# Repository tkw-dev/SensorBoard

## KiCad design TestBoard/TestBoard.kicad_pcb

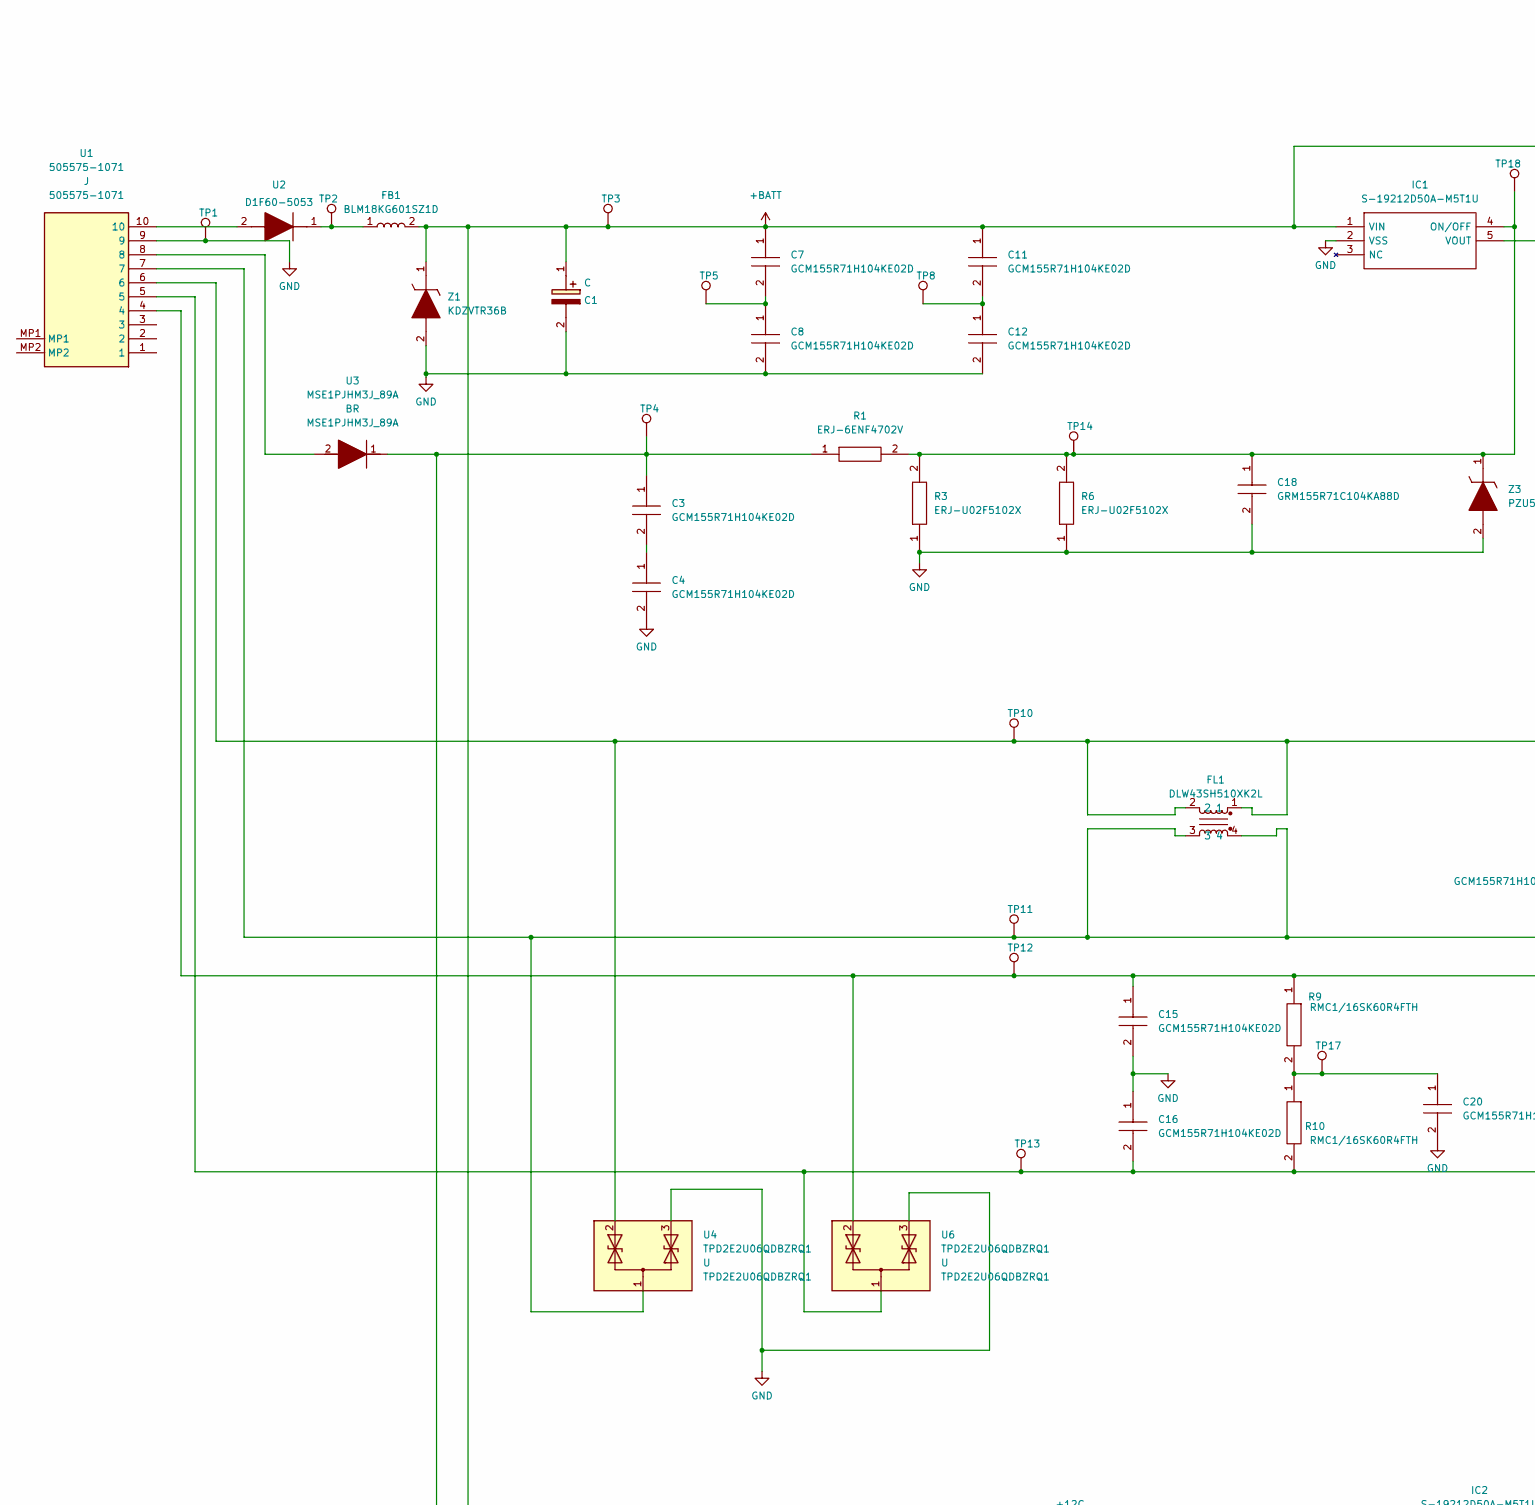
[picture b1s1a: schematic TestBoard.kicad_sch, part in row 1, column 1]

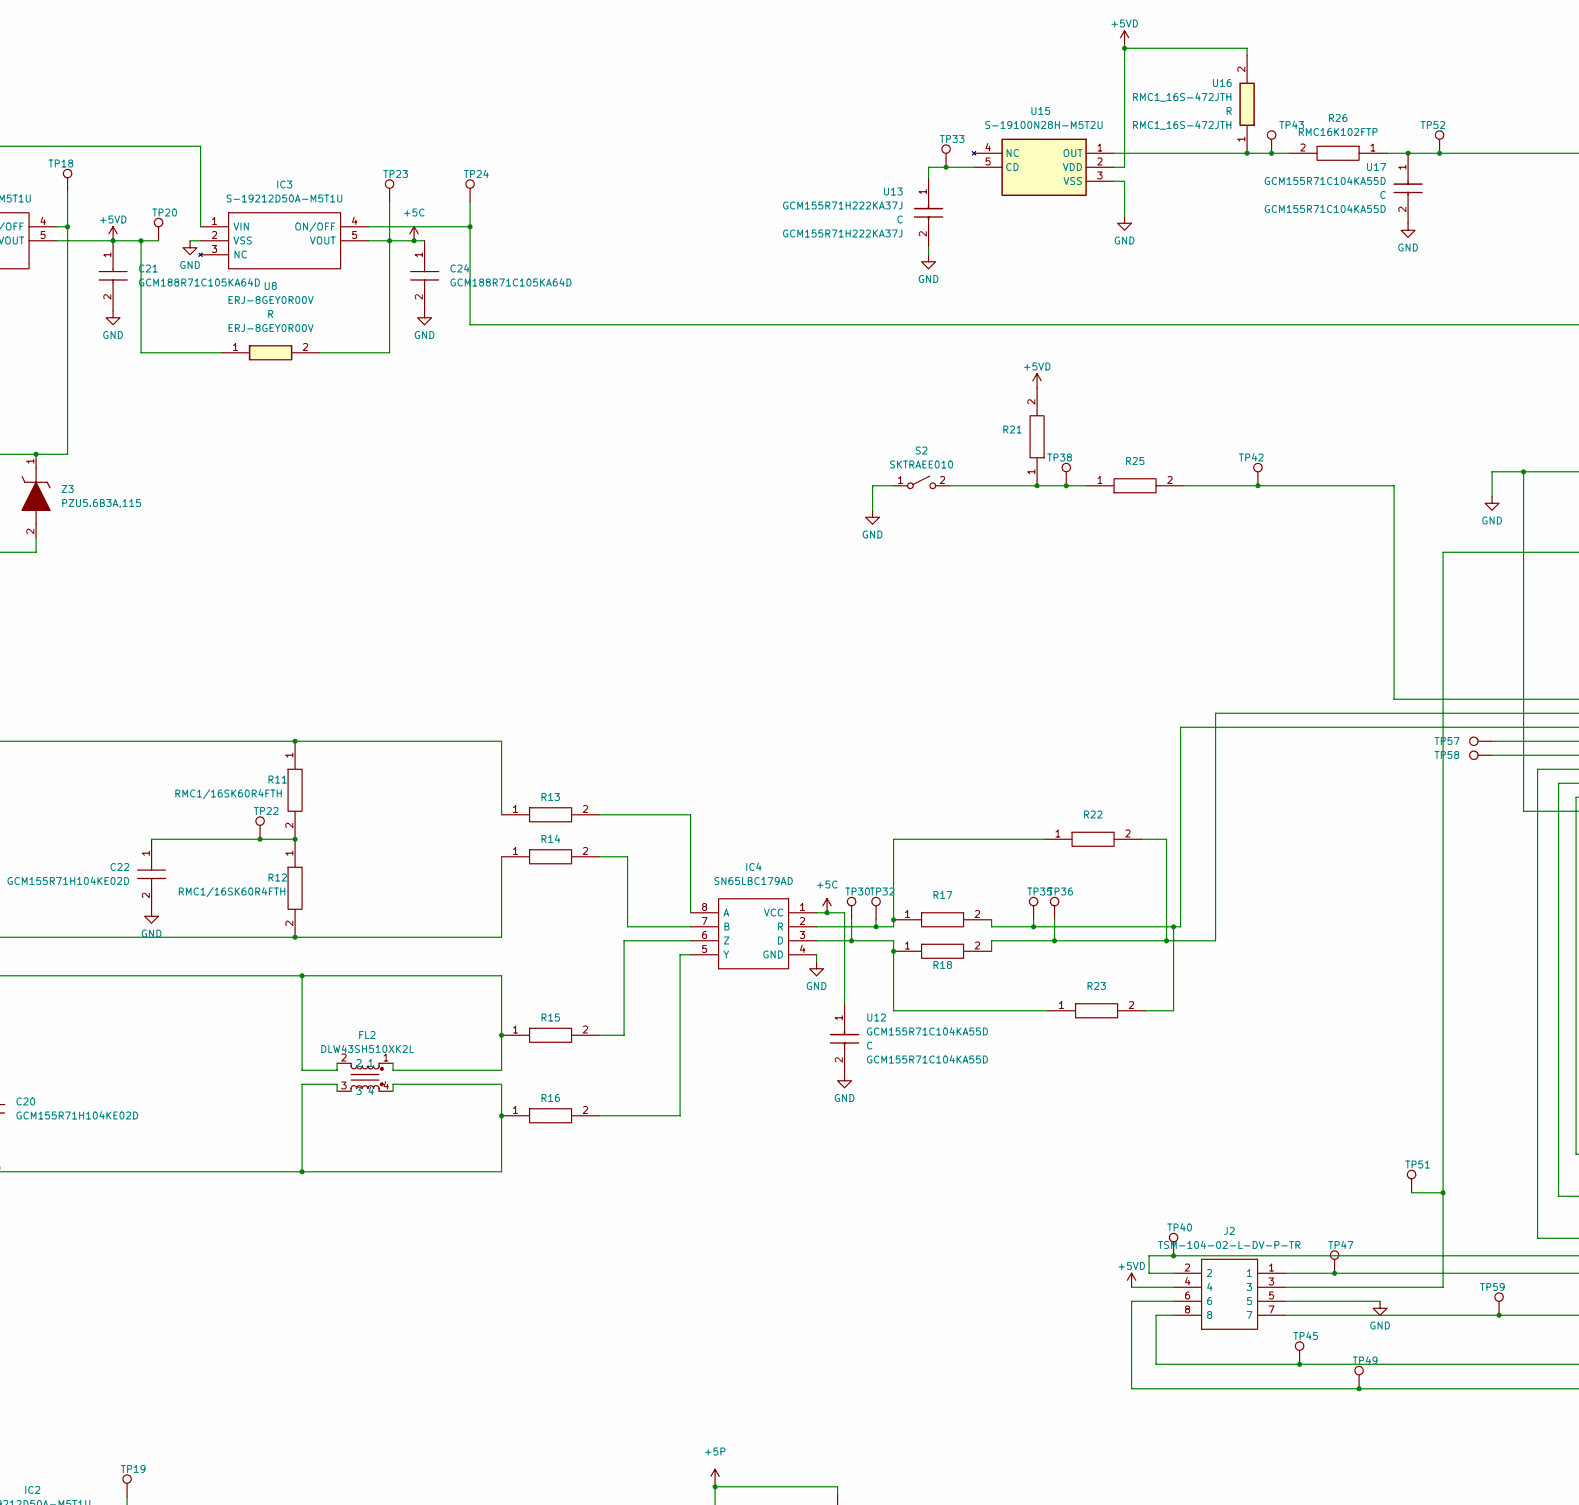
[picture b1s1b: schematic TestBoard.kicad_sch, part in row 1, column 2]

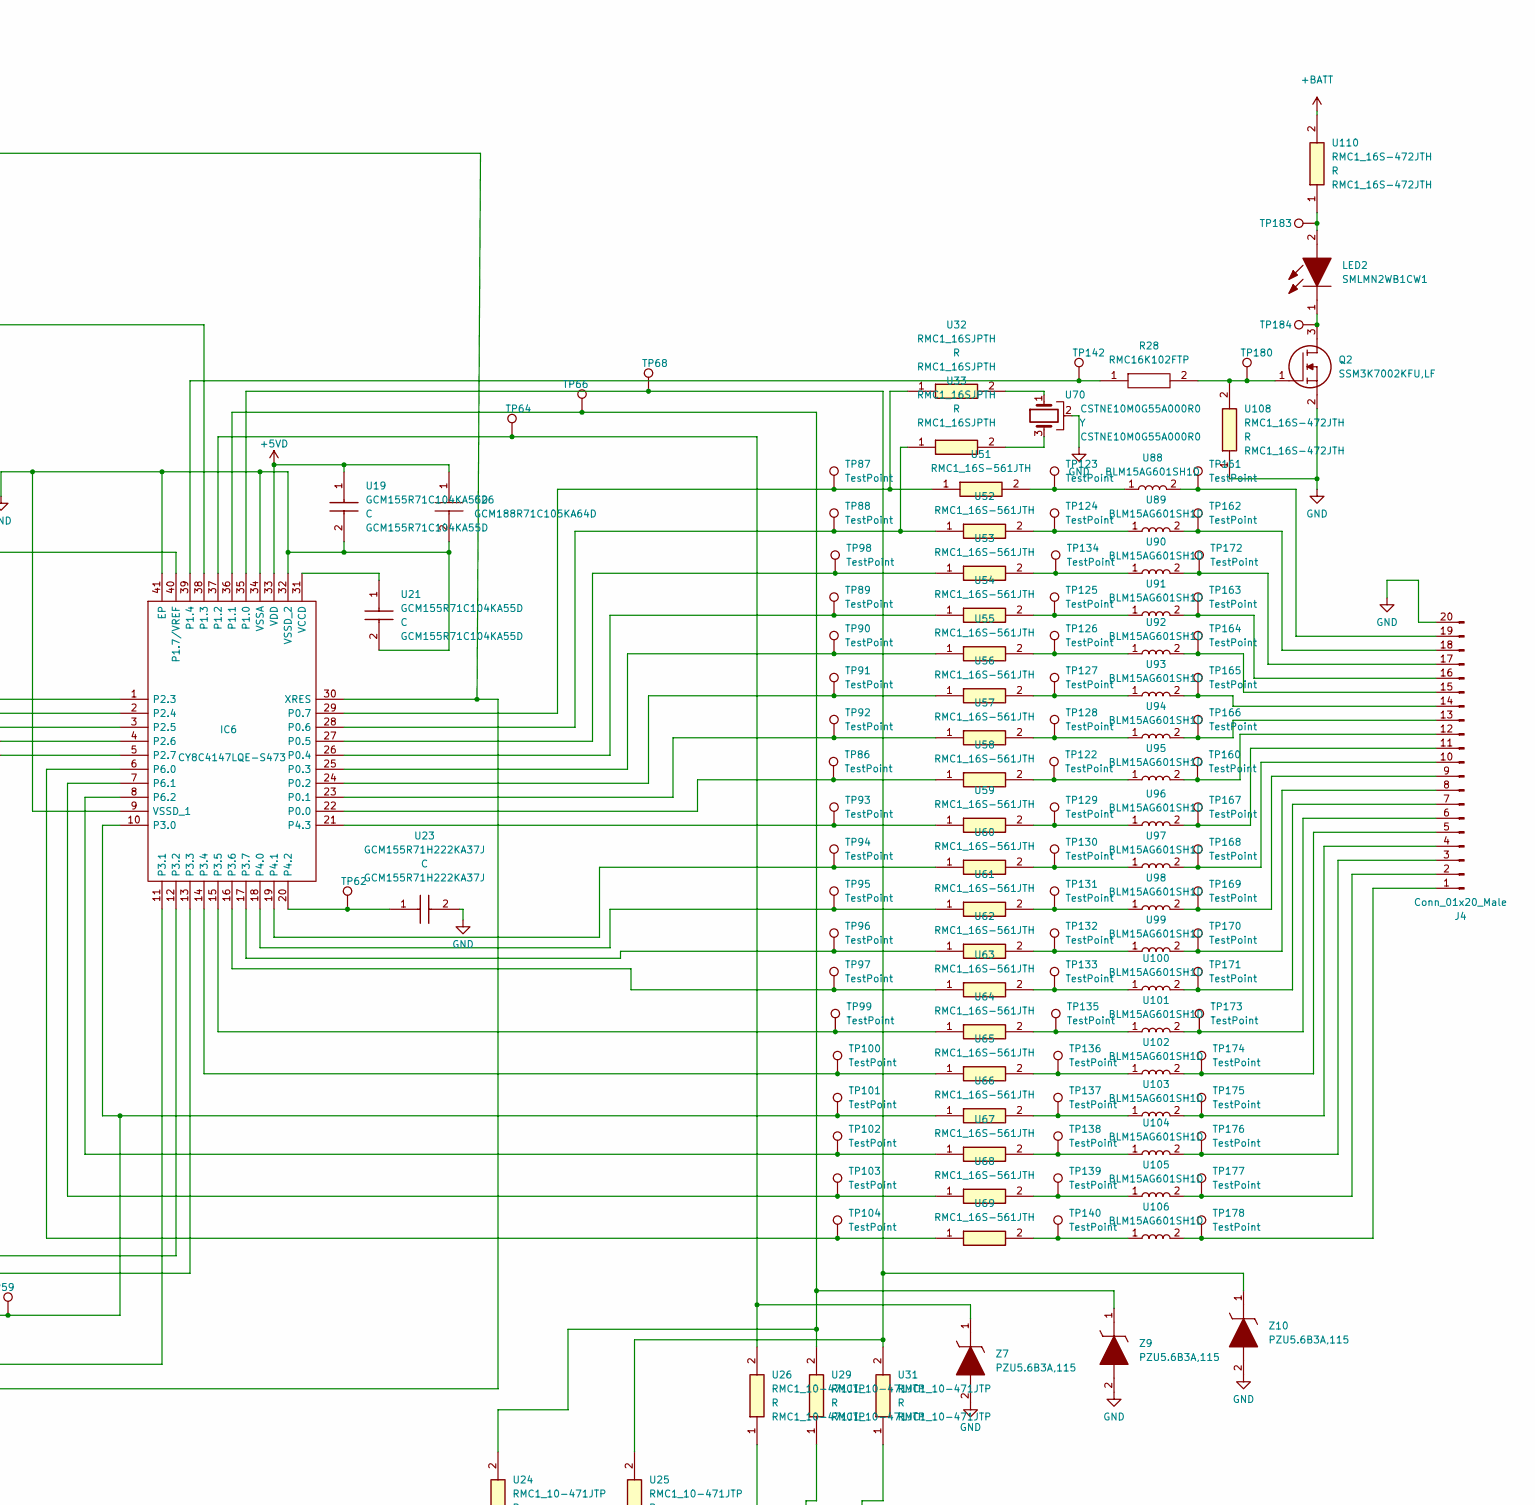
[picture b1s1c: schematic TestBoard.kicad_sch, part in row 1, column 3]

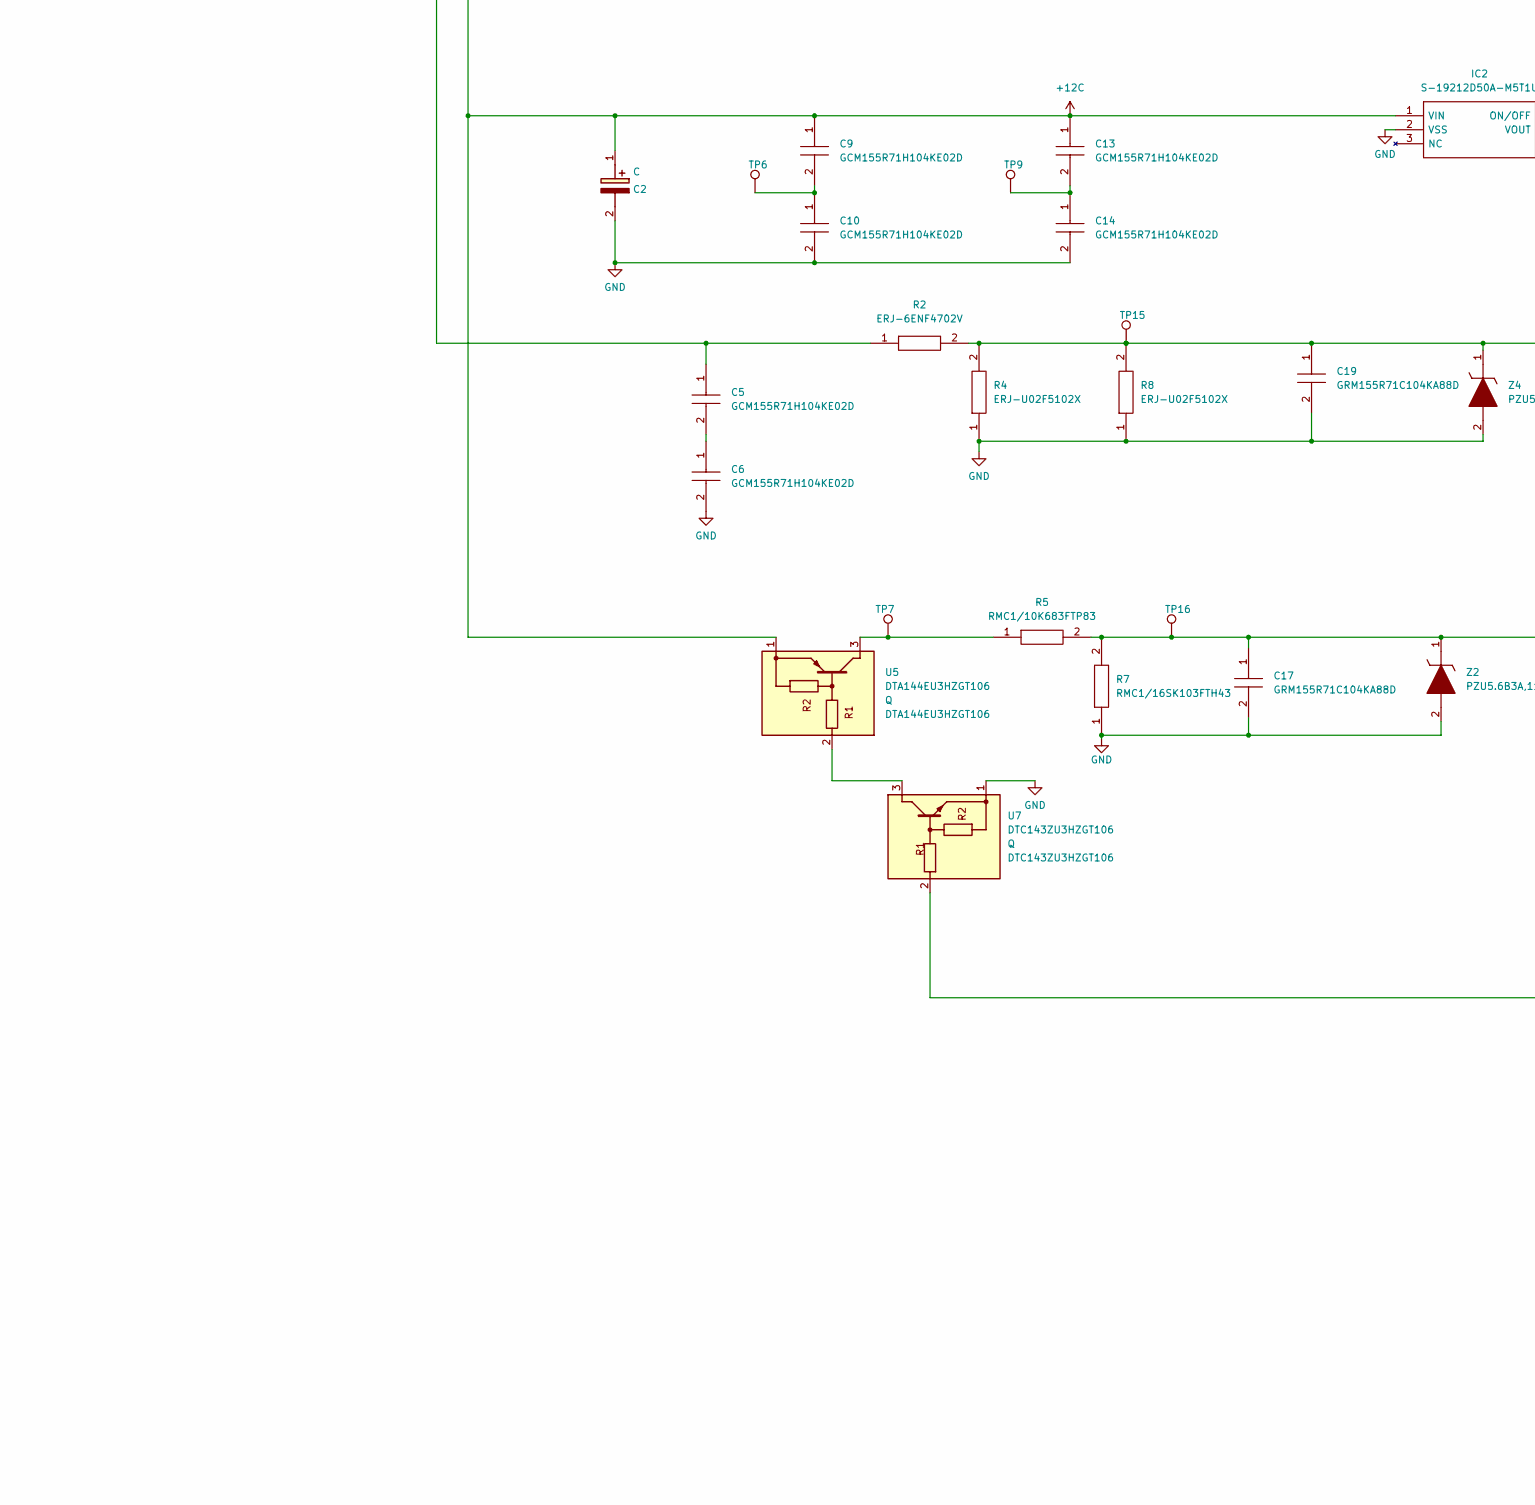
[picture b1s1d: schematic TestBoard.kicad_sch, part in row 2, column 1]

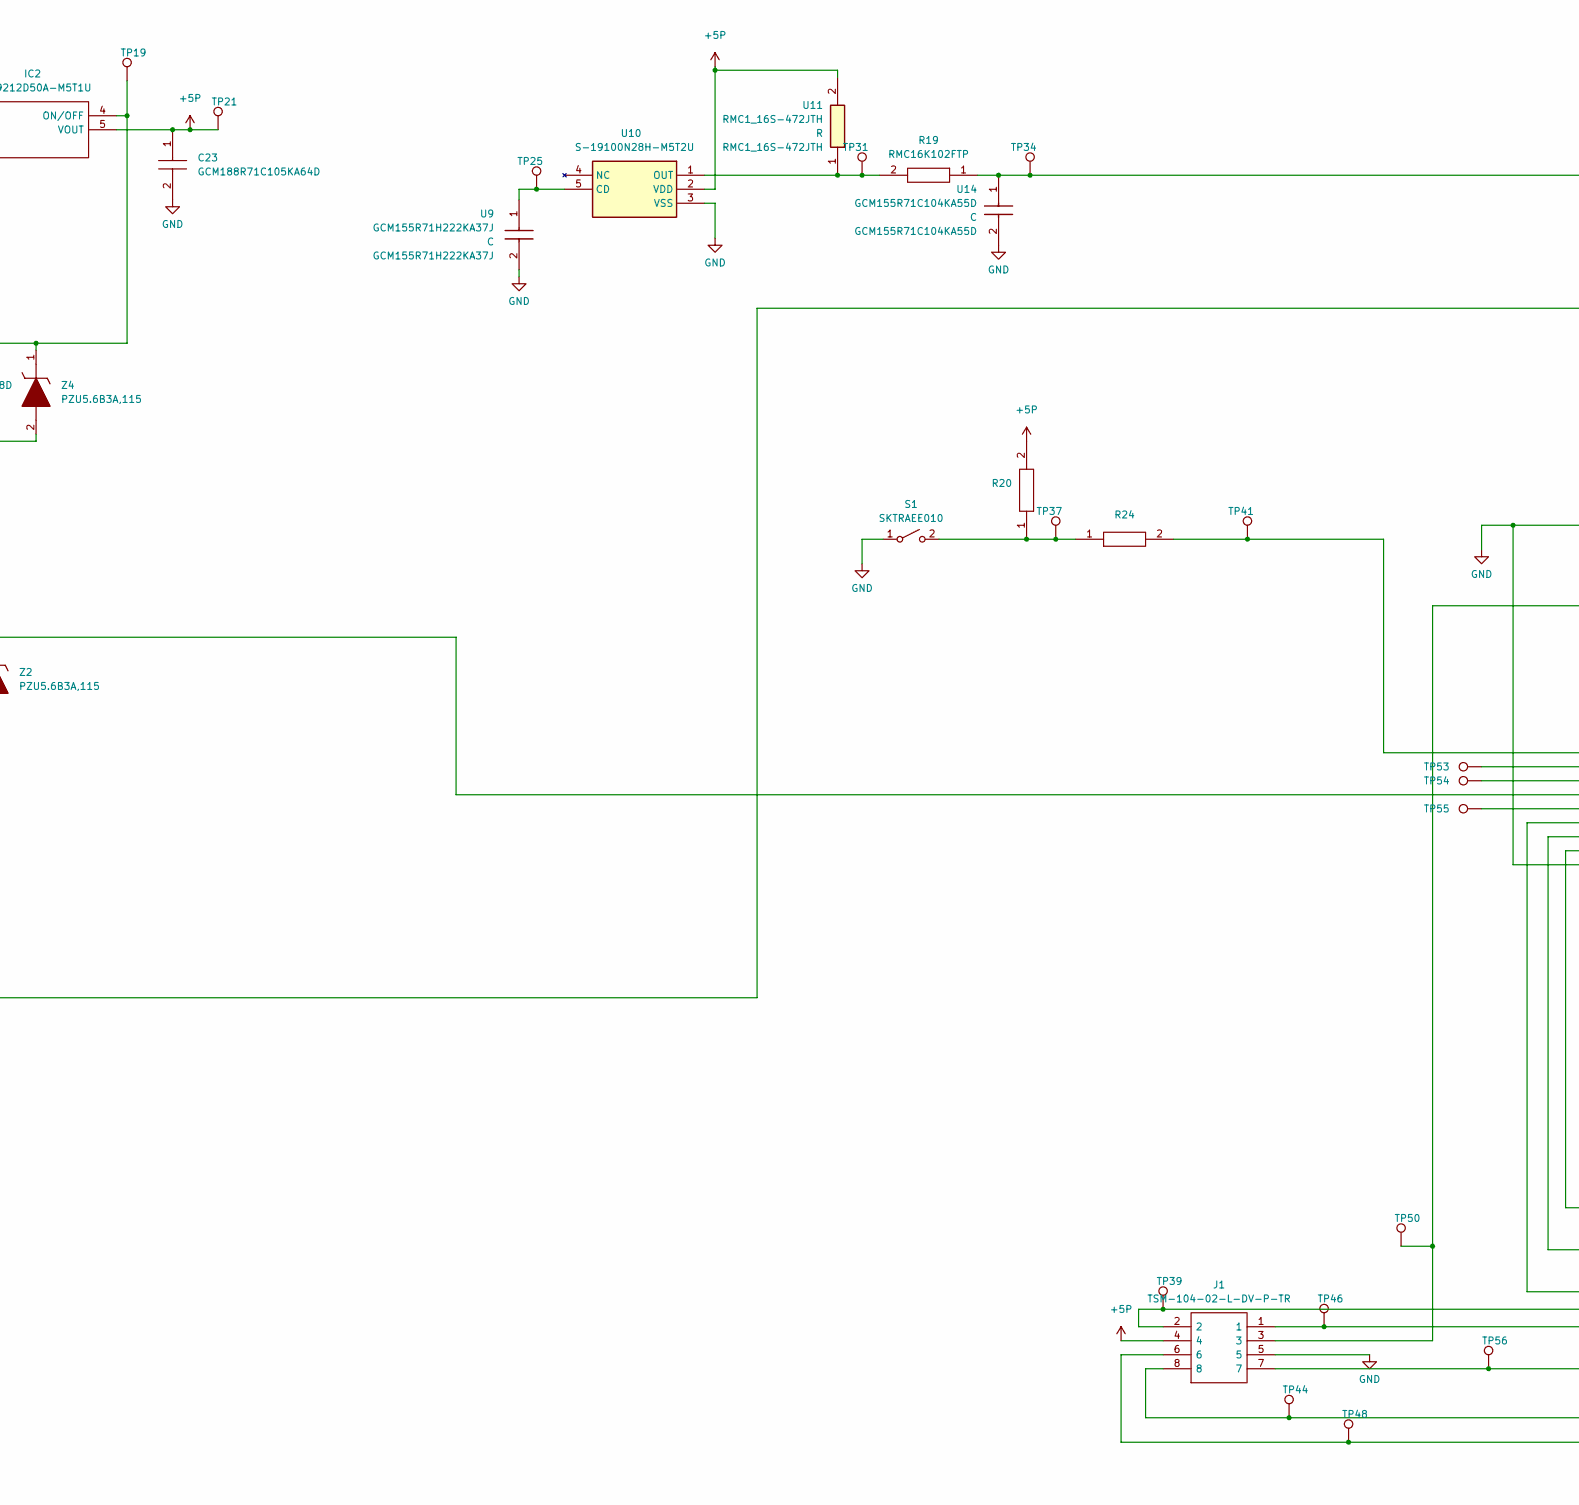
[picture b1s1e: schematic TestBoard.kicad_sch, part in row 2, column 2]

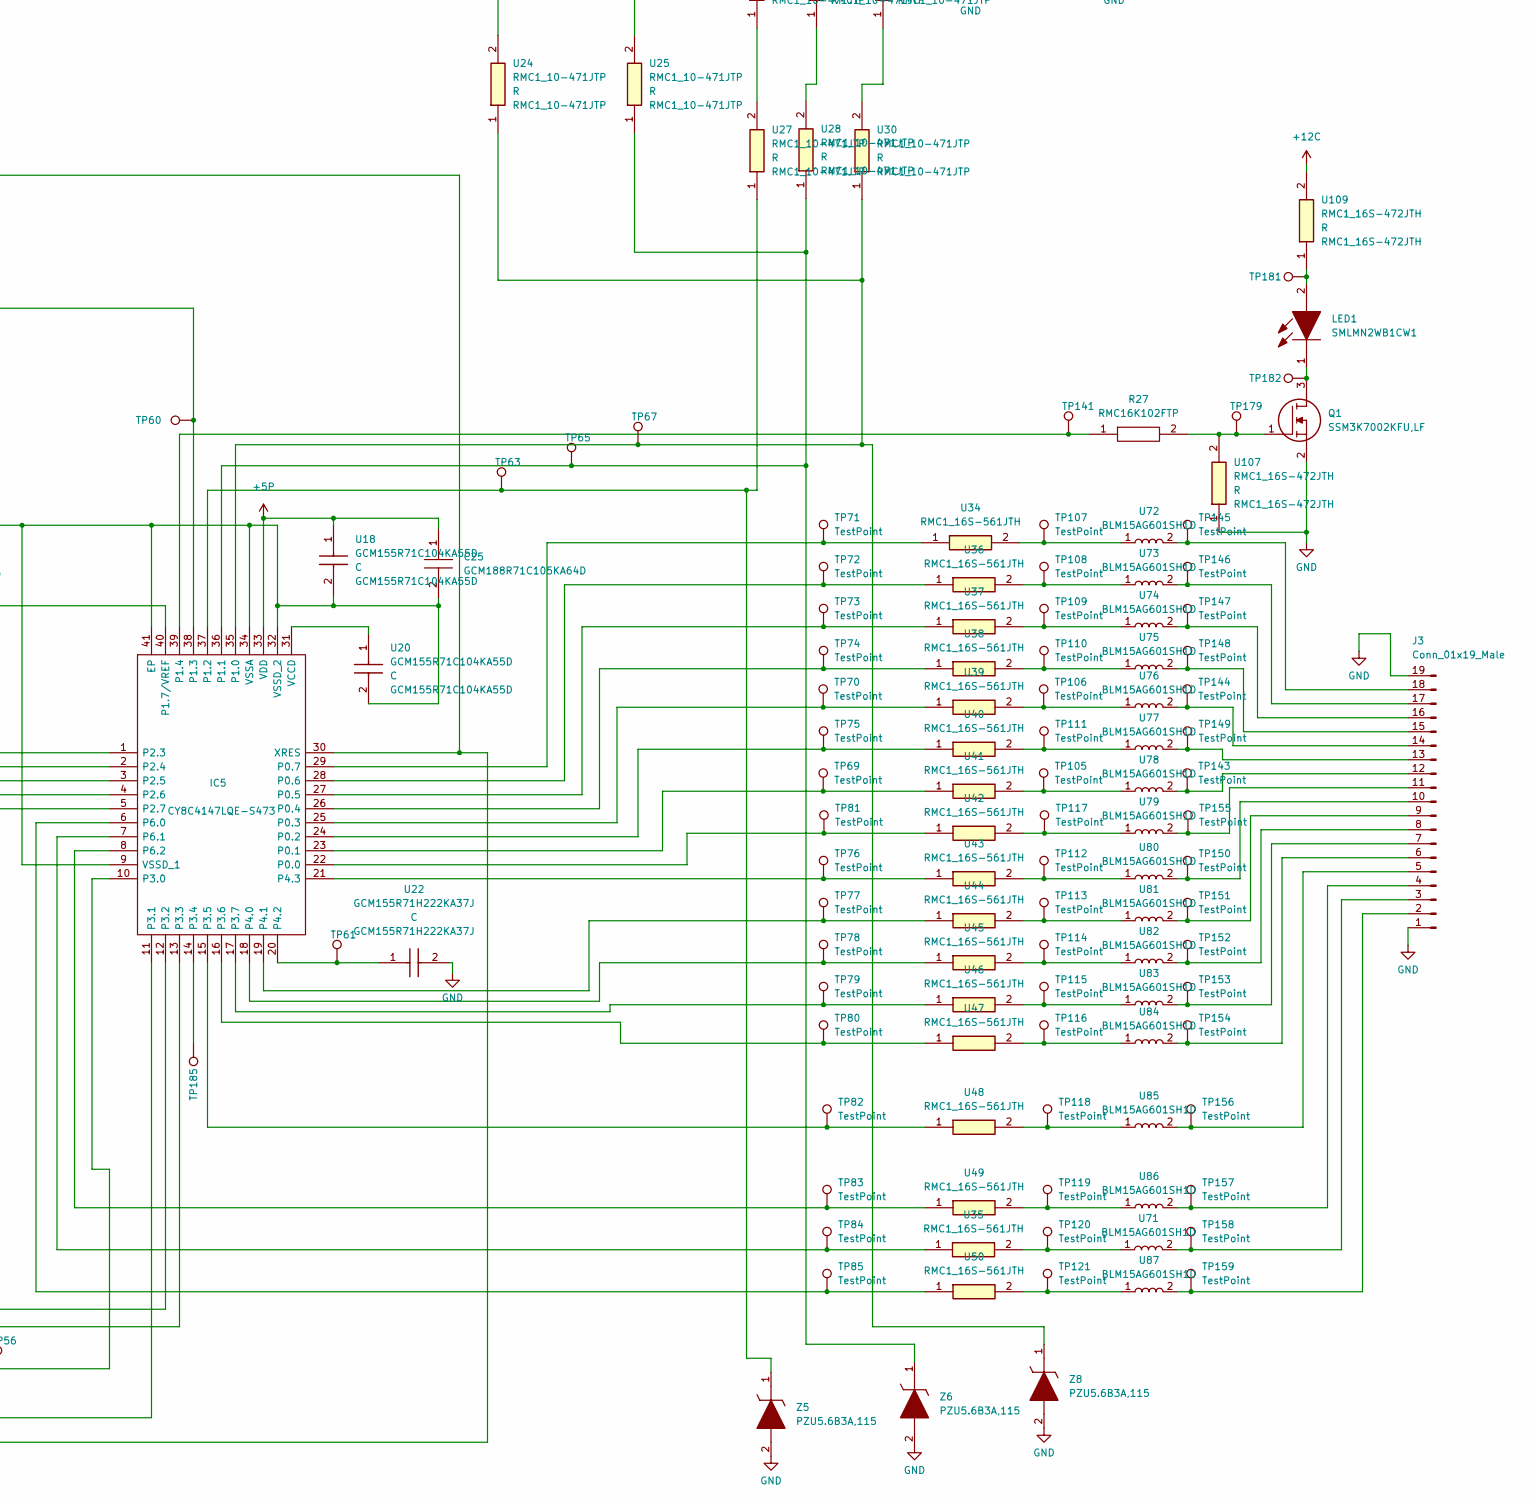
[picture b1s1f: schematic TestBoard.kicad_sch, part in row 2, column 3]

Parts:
C1, C2: RSVVS010M1UBC3001U; CAPAE430X550N; Mouser Part Number 555-RVS-50V010MU-R
C3, C4, C5, C6, C7, C8, C9, C10, C11, C12, C13, C14, C15, C16, C20, C22: GCM155R71H104KE02D; CAPC1005X55N; Mouser Part Number 81-GCM155R71H104KE2D
C17, C18, C19: GRM155R71C104KA88D; CAPC1005X55N; Mouser Part Number N/A
C21, C23, C24, C25, C26: GCM188R71C105KA64D; CAPC1608X90N; Mouser Part Number 81-GCM188R71C105K64D
FB1: BLM18KG601SZ1D; BLM18EG121SH1D; Mouser Part Number 81-BLM18KG601SZ1D
FL1, FL2: DLW43SH510XK2L; DLW43SH110XK2K; Mouser Part Number 81-DLW43SH510XK2L
IC1, IC2, IC3: S-19212D50A-M5T1U; SOT-89-5; Mouser Part Number 628-S19212D50AM5T1U
IC4: SN65LBC179AD; SOIC127P600X175-8N; Mouser Part Number 595-SN65LBC179AD
IC5, IC6: CY8C4147LQE-S473; QFN50P600X600X60-41N-D; Mouser Part Number 727-CY8C4147LQE-S473
J1, J2: TSM-104-02-L-DV-P-TR; TSM-104-YY-ZZZ-DV-P-TR; Manufacturer_Part_Number TSM-104-02-L-DV-P-TR; Mouser Part Number 200-TSM10402LDVPTR
J3: Conn_01x19_Male; PinHeader_1x19_P2.54mm_Horizontal
J4: Conn_01x20_Male; PinHeader_1x20_P2.54mm_Horizontal
LED1, LED2: SMLMN2WB1CW1; LEDC2012X100N; Mouser Part Number 755-SMLMN2WB1CW1C
Q1, Q2: SSM3K7002KFU,LF; SSM3K7002CFULF; Mouser Part Number 757-SSM3K7002KFULF
R1, R2: ERJ-6ENF4702V; ERJ6ENF1000V; Mouser Part Number 667-ERJ-6ENF4702V
R3, R4, R6, R8: ERJ-U02F5102X; ERJS02_U02__0402_; Manufacturer_Part_Number ERJ-U02F5102X
R5: RMC1/10K683FTP83; RESC2012X65N; Mouser Part Number 791-RMC1/10-103JTP
R7, R20, R21, R24, R25: RMC1/16SK103FTH43; RESC1608X55N; Manufacturer_Part_Number RMC16K102FTP
R9, R10, R11, R12: RMC1/16SK60R4FTH; RESC1608X55N; Manufacturer_Part_Number RMC16K270FTP
R13, R14, R15, R16, R17, R18, R22, R23: RMC16K270FTP; RESC1608X55N; Manufacturer_Part_Number RMC16K270FTP
R19, R26, R27, R28: RMC16K102FTP; RESC1608X55N; Manufacturer_Part_Number RMC16K102FTP
S1, S2: SKTRAEE010; Mouser Part Number 688-SKTRAEE010
TP1, TP3, TP4, TP20, TP21, TP39, TP40, TP44, TP45, TP46, TP47, TP48, TP49, TP50, TP51, TP56, TP59: TestPoint; TestPoint_Pad_D2.5mm
TP2, TP5, TP6, TP7, TP8, TP9, TP10, TP11, TP12, TP13, TP14, TP15, TP16, TP17, TP18, TP19, TP22, TP23, TP24, TP25, TP30, TP31, TP32, TP33, TP34, TP35, TP36, TP37, TP38, TP41, TP42, TP43, TP52, TP53, TP54, TP55, TP57, TP58, TP60, TP61, TP62, TP63, TP64, TP65, TP66, TP67, TP68, TP141, TP142, TP179, TP180, TP181, TP182, TP183, TP184, TP185: TestPoint; TestPoint_Pad_D1.0mm
TP69, TP70, TP71, TP72, TP73, TP74, TP75, TP76, TP77, TP78, TP79, TP80, TP81, TP82, TP83, TP84, TP85, TP86, TP87, TP88, TP89, TP90, TP91, TP92, TP93, TP94, TP95, TP96, TP97, TP98, TP99, TP100, TP101, TP102, TP103, TP104, TP105, TP106, TP107, TP108, TP109, TP110, TP111, TP112, TP113, TP114, TP115, TP116, TP117, TP118, TP119, TP120, TP121, TP122, TP123, TP124, TP125, TP126, TP127, TP128, TP129, TP130, TP131, TP132, TP133, TP134, TP135, TP136, TP137, TP138, TP139, TP140, TP143, TP144, TP145, TP146, TP147, TP148, TP149, TP150, TP151, TP152, TP153, TP154, TP155, TP156, TP157, TP158, TP159, TP160, TP161, TP162, TP163, TP164, TP165, TP166, TP167, TP168, TP169, TP170, TP171, TP172, TP173, TP174, TP175, TP176, TP177, TP178: TestPoint; TestPoint_Pad_D0.5mm
U1: 505575-1071; 5055751071; Mouser Part Number 538-505575-1071
U2: D1F60-5053; DIOM5025X200N; Mouser Part Number 627-D1F605053
U3: MSE1PJHM3J_89A; MSE1PJHM3J89A; Manufacturer_Part_Number MSE1PJHM3J/89A; Mouser Part Number 78-MSE1PJHM3J/89A
U4, U6: TPD2E2U06QDBZRQ1; SOT95P237X95-3N; Mouser Part Number 595-TPD2E2U06QDBZRQ1
U5: DTA144EU3HZGT106; Manufacturer_Part_Number DTA144EU3HZGT106; Mouser Part Number 755-DTA144EU3HZGT106
U7: DTC143ZU3HZGT106; Mouser Part Number 755-DTC143ZU3HZGT106
U8: ERJ-8GEY0R00V; ERJ8ENF1000V; Mouser Part Number 667-ERJ-8GEY0R00V
U9, U13, U22, U23: GCM155R71H222KA37J; CAPC1005X55N; Mouser Part Number 81-GCM155R71H222KA7J
U10, U15: S-19100N28H-M5T2U; SOT95P275X130-5N; Manufacturer_Part_Number S-19100N28H-M5T2U
U11, U16, U107, U108, U109, U110: RMC1_16S-472JTH; RESC1005X40N; Manufacturer_Part_Number RMC1/16S-472JTH; Mouser Part Number 791-RMC1/16S-472JTH
U12, U14, U17, U18, U19, U20, U21: GCM155R71C104KA55D; CAPC1005X55N; Mouser Part Number 81-GCM155R71C104KA5D
U24, U25, U26, U27, U28, U29, U30, U31: RMC1_10-471JTP; RESC2012X65N; Manufacturer_Part_Number RMC1/10-471JTP
U32, U33: RMC1_16SJPTH; RESC1005X40N; Mouser Part Number 791-RMC1/16SJPTH
U34, U35, U36, U37, U38, U39, U40, U41, U42, U43, U44, U45, U46, U47, U48, U49, U50, U51, U52, U53, U54, U55, U56, U57, U58, U59, U60, U61, U62, U63, U64, U65, U66, U67, U68, U69: RMC1_16S-561JTH; RESC1005X40N; Manufacturer_Part_Number RMC1/16S-561JTH; Mouser Part Number 791-RMC1/16S-561JTH
U70: CSTNE10M0G55A000R0; Mouser Part Number 81-CSTNE10M0G55A000R
U71, U72, U73, U74, U75, U76, U77, U78, U79, U80, U81, U82, U83, U84, U85, U86, U87, U88, U89, U90, U91, U92, U93, U94, U95, U96, U97, U98, U99, U100, U101, U102, U103, U104, U105, U106: BLM15AG601SH1D; NFZ15SG152SN10B; Mouser Part Number 81-BLM15AG601SH1D
Z1: KDZVTR36B; Mouser Part Number 755-KDZVTR36B
Z2, Z3, Z4, Z5, Z6, Z7, Z8, Z9, Z10: PZU5.6B3A,115; SOD2512X110N; Mouser Part Number 771-PZU5.6B3A,115

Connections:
+5C: C24.1, IC3.5 (VOUT), IC4.1 (VCC), TP23.1, U8.2, U12.1
+5P: C23.1, C25.1, IC2.5 (VOUT), IC5.33 (VDD), J1.4, R20.2, TP21.1, U10.2 (VDD), U11.2, U18.1
+5VD: C21.1, C26.1, IC1.5 (VOUT), IC6.33 (VDD), J2.4, R21.2, TP20.1, U8.1, U15.2 (VDD), U16.2, U19.1
+BATT: C1.1 (+), C2.1 (+), C7.1, C9.1, C11.1, C13.1, FB1.2, IC1.1 (VIN), IC2.1 (VIN), IC3.1 (VIN), TP3.1, U5.1 (E), U109.2, U110.2, Z1.1
GND: C1.2 (-), C2.2 (-), C4.2, C6.2, C8.2, C10.2, C12.2, C14.2, C15.2, C16.1, C17.2, C18.2, C19.2, C20.2, C21.2, C22.2, C23.2, C24.2, C25.2, C26.2, IC1.2 (VSS), IC2.2 (VSS), IC3.2 (VSS), IC4.4 (GND), IC5.9 (VSSD_1), IC5.32 (VSSD_2), IC5.34 (VSSA), IC5.41 (EP), IC6.9 (VSSD_1), IC6.32 (VSSD_2), IC6.34 (VSSA), IC6.41 (EP), J1.5, J2.5, J3.1, J3.19, J4.20, Q1.2, Q2.2, R3.1, R4.1, R6.1, R7.1, R8.1, S1.1, S2.1, TP1.1, U1.9, U4.3, U6.3, U7.1 (E), U9.2, U10.3 (VSS), U12.2, U13.2, U14.2, U15.3 (VSS), U17.2, U18.2, U19.2, U20.2, U21.2, U22.2, U23.2, U70.2, U107.1, U108.1, Z1.2, Z2.2, Z3.2, Z4.2, Z5.2, Z6.2, Z7.2, Z8.2, Z9.2, Z10.2
unnamed: C3.1, C5.1, R1.1, R2.1, TP4.1, U3.1
unnamed: C3.2, C4.1
unnamed: C5.2, C6.1
unnamed: C7.2, C8.1, TP5.1
unnamed: C9.2, C10.1, TP6.1
unnamed: C11.2, C12.1, TP8.1
unnamed: C13.2, C14.1, TP9.1
unnamed: C15.1, FL2.1, FL2.2, R9.1, R15.1, TP12.1, U1.4, U6.2
unnamed: C16.2, FL2.3, FL2.4, R10.2, R16.1, TP13.1, U1.5, U6.1
unnamed: C17.1, IC5.4 (P2.6), R5.2, R7.2, TP16.1, Z2.1
unnamed: C18.1, IC1.4 (ON/OFF), R1.2, R3.2, R6.2, TP14.1, TP18.1, Z3.1
unnamed: C19.1, IC2.4 (ON/OFF), R2.2, R4.2, R8.2, TP15.1, TP19.1, Z4.1
unnamed: C20.1, R9.2, R10.1, TP17.1
unnamed: C22.1, R11.2, R12.1, TP22.1
unnamed: FB1.1, TP2.1, U2.1 (K)
unnamed: FL1.1, FL1.2, R11.1, R13.1, TP10.1, U1.6, U4.2
unnamed: FL1.3, FL1.4, R12.2, R14.1, TP11.1, U1.7, U4.1
unnamed: IC3.4 (ON/OFF), IC6.38 (P1.3), TP24.1
unnamed: IC4.2 (R), R17.1, R22.1, TP32.1
unnamed: IC4.3 (D), R18.1, R23.1, TP30.1
unnamed: IC4.5 (Y), R16.2
unnamed: IC4.6 (Z), R15.2
unnamed: IC4.7 (B), R14.2
unnamed: IC4.8 (A), R13.2
unnamed: IC5.1 (P2.3), R24.2, TP41.1
unnamed: IC5.2 (P2.4), TP53.1
unnamed: IC5.3 (P2.5), TP54.1
unnamed: IC5.5 (P2.7), TP55.1
unnamed: IC5.6 (P6.0), TP85.1, U50.1
unnamed: IC5.7 (P6.1), TP84.1, U35.1
unnamed: IC5.8 (P6.2), TP83.1, U49.1
unnamed: IC5.10 (P3.0), J1.7, TP56.1
unnamed: IC5.11 (P3.1), J1.8, TP44.1
unnamed: IC5.12 (P3.2), J1.2, TP39.1
unnamed: IC5.13 (P3.3), J1.1, TP46.1
unnamed: IC5.14 (P3.4), TP185.1
unnamed: IC5.16 (P3.6), TP80.1, U47.1
unnamed: IC5.17 (P3.7), TP79.1, U46.1
unnamed: IC5.18 (P4.0), TP78.1, U45.1
unnamed: IC5.19 (P4.1), TP77.1, U44.1
unnamed: IC5.20 (P4.2), TP61.1, U22.1
unnamed: IC5.21 (P4.3), TP76.1, U43.1
unnamed: IC5.22 (P0.0), TP81.1, U42.1
unnamed: IC5.23 (P0.1), TP69.1, U41.1
unnamed: IC5.24 (P0.2), TP75.1, U40.1
unnamed: IC5.25 (P0.3), TP70.1, U39.1
unnamed: IC5.26 (P0.4), TP74.1, U38.1
unnamed: IC5.27 (P0.5), TP73.1, U37.1
unnamed: IC5.28 (P0.6), TP72.1, U36.1
unnamed: IC5.29 (P0.7), TP71.1, U34.1
unnamed: IC5.30 (XRES), J1.6, R19.1, TP34.1, TP48.1, U14.1
unnamed: IC5.31 (VCCD), U20.1
unnamed: IC5.35 (P1.0), TP67.1, U24.1, U30.1, Z8.1
unnamed: IC5.36 (P1.1), TP65.1, U25.1, U28.1, Z6.1
unnamed: IC5.37 (P1.2), TP63.1, U27.1, Z5.1
unnamed: IC5.38 (P1.3), TP60.1, U7.2 (B)
unnamed: IC5.39 (P1.4), R27.1, TP141.1
unnamed: IC5.40 (P1.7/VREF), J1.3, TP50.1
unnamed: IC6.1 (P2.3), R25.2, TP42.1
unnamed: IC6.2 (P2.4), R18.2, R22.2, TP36.1
unnamed: IC6.3 (P2.5), R17.2, R23.2, TP35.1
unnamed: IC6.4 (P2.6), TP57.1
unnamed: IC6.5 (P2.7), TP58.1
unnamed: IC6.6 (P6.0), TP104.1, U69.1
unnamed: IC6.7 (P6.1), TP103.1, U68.1
unnamed: IC6.8 (P6.2), TP102.1, U67.1
unnamed: IC6.10 (P3.0), J2.7, TP59.1, TP101.1, U66.1
unnamed: IC6.11 (P3.1), J2.8, TP45.1
unnamed: IC6.12 (P3.2), J2.2, TP40.1
unnamed: IC6.13 (P3.3), J2.1, TP47.1
unnamed: IC6.14 (P3.4), TP100.1, U65.1
unnamed: IC6.15 (P3.5), TP99.1, U64.1
unnamed: IC6.16 (P3.6), TP97.1, U63.1
unnamed: IC6.17 (P3.7), TP96.1, U62.1
unnamed: IC6.18 (P4.0), TP95.1, U61.1
unnamed: IC6.19 (P4.1), TP94.1, U60.1
unnamed: IC6.20 (P4.2), TP62.1, U23.1
unnamed: IC6.21 (P4.3), TP93.1, U59.1
unnamed: IC6.22 (P0.0), TP86.1, U58.1
unnamed: IC6.23 (P0.1), TP92.1, U57.1
unnamed: IC6.24 (P0.2), TP91.1, U56.1
unnamed: IC6.25 (P0.3), TP90.1, U55.1
unnamed: IC6.26 (P0.4), TP89.1, U54.1
unnamed: IC6.27 (P0.5), TP98.1, U53.1
unnamed: IC6.28 (P0.6), TP88.1, U33.1, U52.1
unnamed: IC6.29 (P0.7), TP87.1, U32.1, U51.1
unnamed: IC6.30 (XRES), J2.6, R26.1, TP49.1, TP52.1, U17.1
unnamed: IC6.31 (VCCD), U21.1
unnamed: IC6.35 (P1.0), TP68.1, U25.2, U31.2, Z10.1
unnamed: IC6.36 (P1.1), TP66.1, U24.2, U29.2, Z9.1
unnamed: IC6.37 (P1.2), TP64.1, U26.2, Z7.1
unnamed: IC6.39 (P1.4), R28.1, TP142.1
unnamed: IC6.40 (P1.7/VREF), J2.3, TP51.1
unnamed: J3.2, TP159.1, U87.2
unnamed: J3.3, TP158.1, U71.2
unnamed: J3.4, TP157.1, U86.2
unnamed: J3.5, TP156.1, U85.2
unnamed: J3.6, TP154.1, U84.2
unnamed: J3.7, TP153.1, U83.2
unnamed: J3.8, TP152.1, U82.2
unnamed: J3.9, TP151.1, U81.2
unnamed: J3.10, TP150.1, U80.2
unnamed: J3.11, TP155.1, U79.2
unnamed: J3.12, TP143.1, U78.2
unnamed: J3.13, TP149.1, U77.2
unnamed: J3.14, TP144.1, U76.2
unnamed: J3.15, TP148.1, U75.2
unnamed: J3.16, TP147.1, U74.2
unnamed: J3.17, TP146.1, U73.2
unnamed: J3.18, TP145.1, U72.2
unnamed: J4.1, TP178.1, U106.2
unnamed: J4.2, TP177.1, U105.2
unnamed: J4.3, TP176.1, U104.2
unnamed: J4.4, TP175.1, U103.2
unnamed: J4.5, TP174.1, U102.2
unnamed: J4.6, TP173.1, U101.2
unnamed: J4.7, TP171.1, U100.2
unnamed: J4.8, TP170.1, U99.2
unnamed: J4.9, TP169.1, U98.2
unnamed: J4.10, TP168.1, U97.2
unnamed: J4.11, TP167.1, U96.2
unnamed: J4.12, TP160.1, U95.2
unnamed: J4.13, TP166.1, U94.2
unnamed: J4.14, TP165.1, U93.2
unnamed: J4.15, TP164.1, U92.2
unnamed: J4.16, TP163.1, U91.2
unnamed: J4.17, TP172.1, U90.2
unnamed: J4.18, TP162.1, U89.2
unnamed: J4.19, TP161.1, U88.2
unnamed: Q1.1, R27.2, TP179.1, U107.2
unnamed: LED1.1, Q1.3, TP182.1
unnamed: Q2.1, R28.2, TP180.1, U108.2
unnamed: LED2.1, Q2.3, TP184.1
unnamed: R5.1, TP7.1, U5.3 (C)
unnamed: R19.2, TP31.1, U10.1 (OUT), U11.1
unnamed: R20.1, R24.1, S1.2, TP37.1
unnamed: R21.1, R25.1, S2.2, TP38.1
unnamed: R26.2, TP43.1, U15.1 (OUT), U16.1
unnamed: TP25.1, U9.1, U10.5 (CD)
unnamed: TP33.1, U13.1, U15.5 (CD)
unnamed: IC5.15 (P3.5), TP82.1, U48.1
unnamed: TP105.1, U41.2, U78.1
unnamed: TP106.1, U39.2, U76.1
unnamed: TP107.1, U34.2, U72.1
unnamed: TP108.1, U36.2, U73.1
unnamed: TP109.1, U37.2, U74.1
unnamed: TP110.1, U38.2, U75.1
unnamed: TP111.1, U40.2, U77.1
unnamed: TP112.1, U43.2, U80.1
unnamed: TP113.1, U44.2, U81.1
unnamed: TP114.1, U45.2, U82.1
unnamed: TP115.1, U46.2, U83.1
unnamed: TP116.1, U47.2, U84.1
unnamed: TP117.1, U42.2, U79.1
unnamed: TP118.1, U48.2, U85.1
unnamed: TP119.1, U49.2, U86.1
unnamed: TP120.1, U35.2, U71.1
unnamed: TP121.1, U50.2, U87.1
unnamed: TP122.1, U58.2, U95.1
unnamed: TP123.1, U51.2, U88.1
unnamed: TP124.1, U52.2, U89.1
unnamed: TP125.1, U54.2, U91.1
unnamed: TP126.1, U55.2, U92.1
unnamed: TP127.1, U56.2, U93.1
unnamed: TP128.1, U57.2, U94.1
unnamed: TP129.1, U59.2, U96.1
unnamed: TP130.1, U60.2, U97.1
unnamed: TP131.1, U61.2, U98.1
unnamed: TP132.1, U62.2, U99.1
unnamed: TP133.1, U63.2, U100.1
unnamed: TP134.1, U53.2, U90.1
unnamed: TP135.1, U64.2, U101.1
unnamed: TP136.1, U65.2, U102.1
unnamed: TP137.1, U66.2, U103.1
unnamed: TP138.1, U67.2, U104.1
unnamed: TP139.1, U68.2, U105.1
unnamed: TP140.1, U69.2, U106.1
unnamed: LED1.2, TP181.1, U109.1
unnamed: U1.8, U3.2
unnamed: U1.10, U2.2 (A)
unnamed: U5.2 (B), U7.3 (C)
unnamed: U26.1, U27.2
unnamed: U28.2, U29.1
unnamed: U30.2, U31.1
unnamed: U32.2, U70.1
unnamed: U33.2, U70.3
unnamed: LED2.2, TP183.1, U110.1

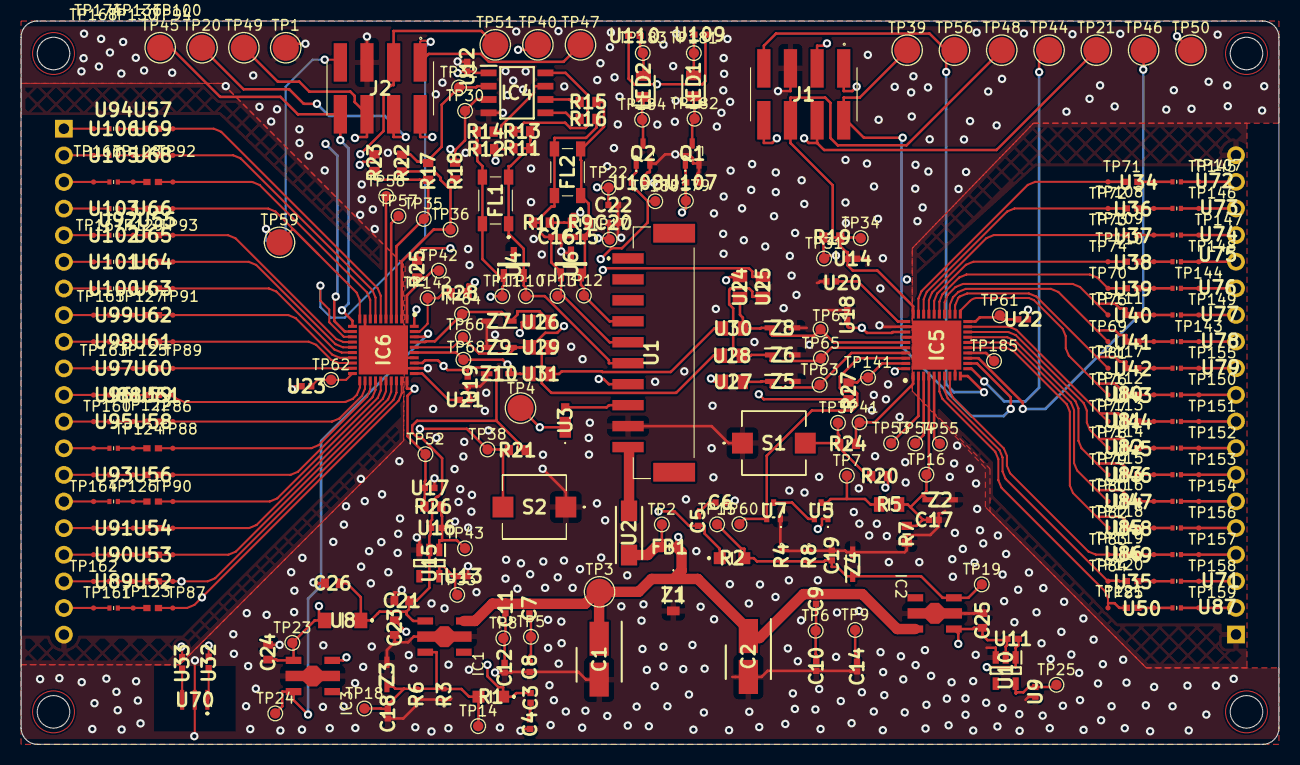
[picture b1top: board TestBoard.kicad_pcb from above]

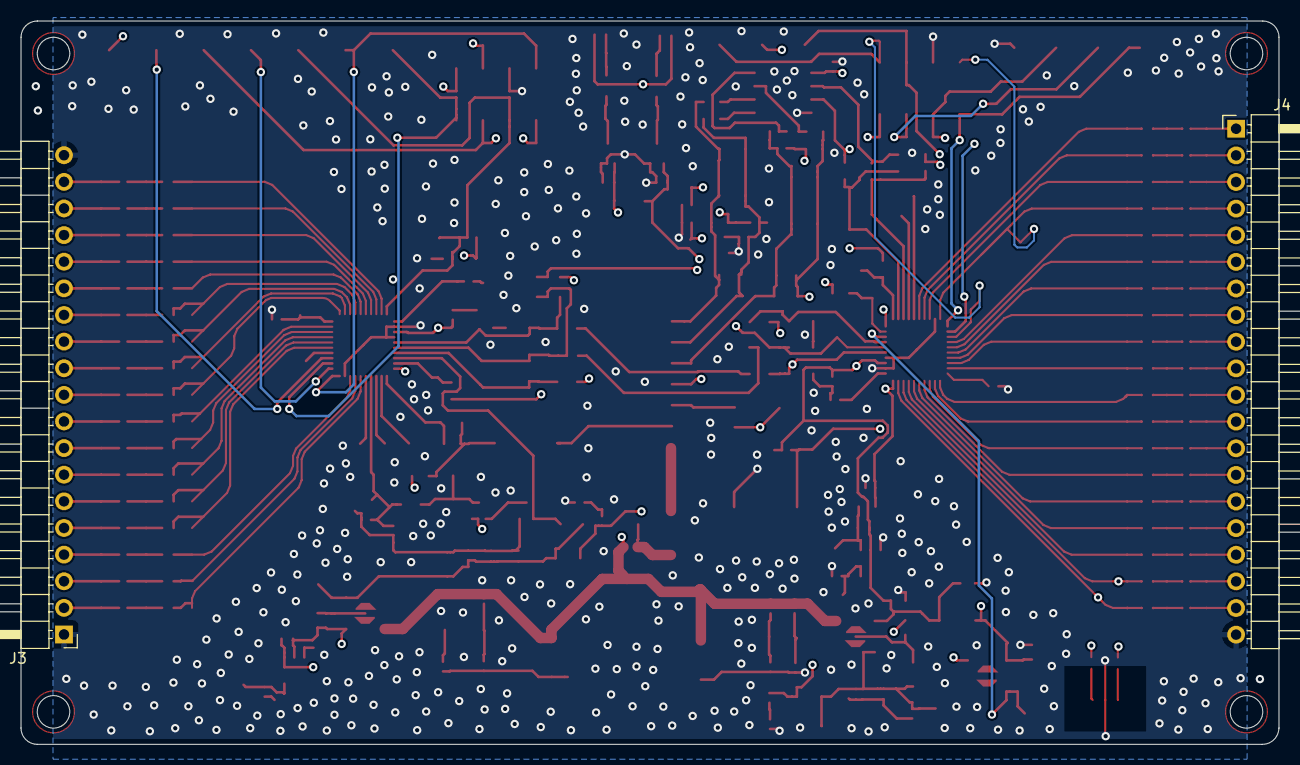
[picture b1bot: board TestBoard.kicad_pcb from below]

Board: 4 copper layers, 120.0 x 69.0 mm, 373 parts (2 on the bottom side), 192 nets.

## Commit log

2023-09-17 socket
2023-10-11 test
2024-03-10 hoge
